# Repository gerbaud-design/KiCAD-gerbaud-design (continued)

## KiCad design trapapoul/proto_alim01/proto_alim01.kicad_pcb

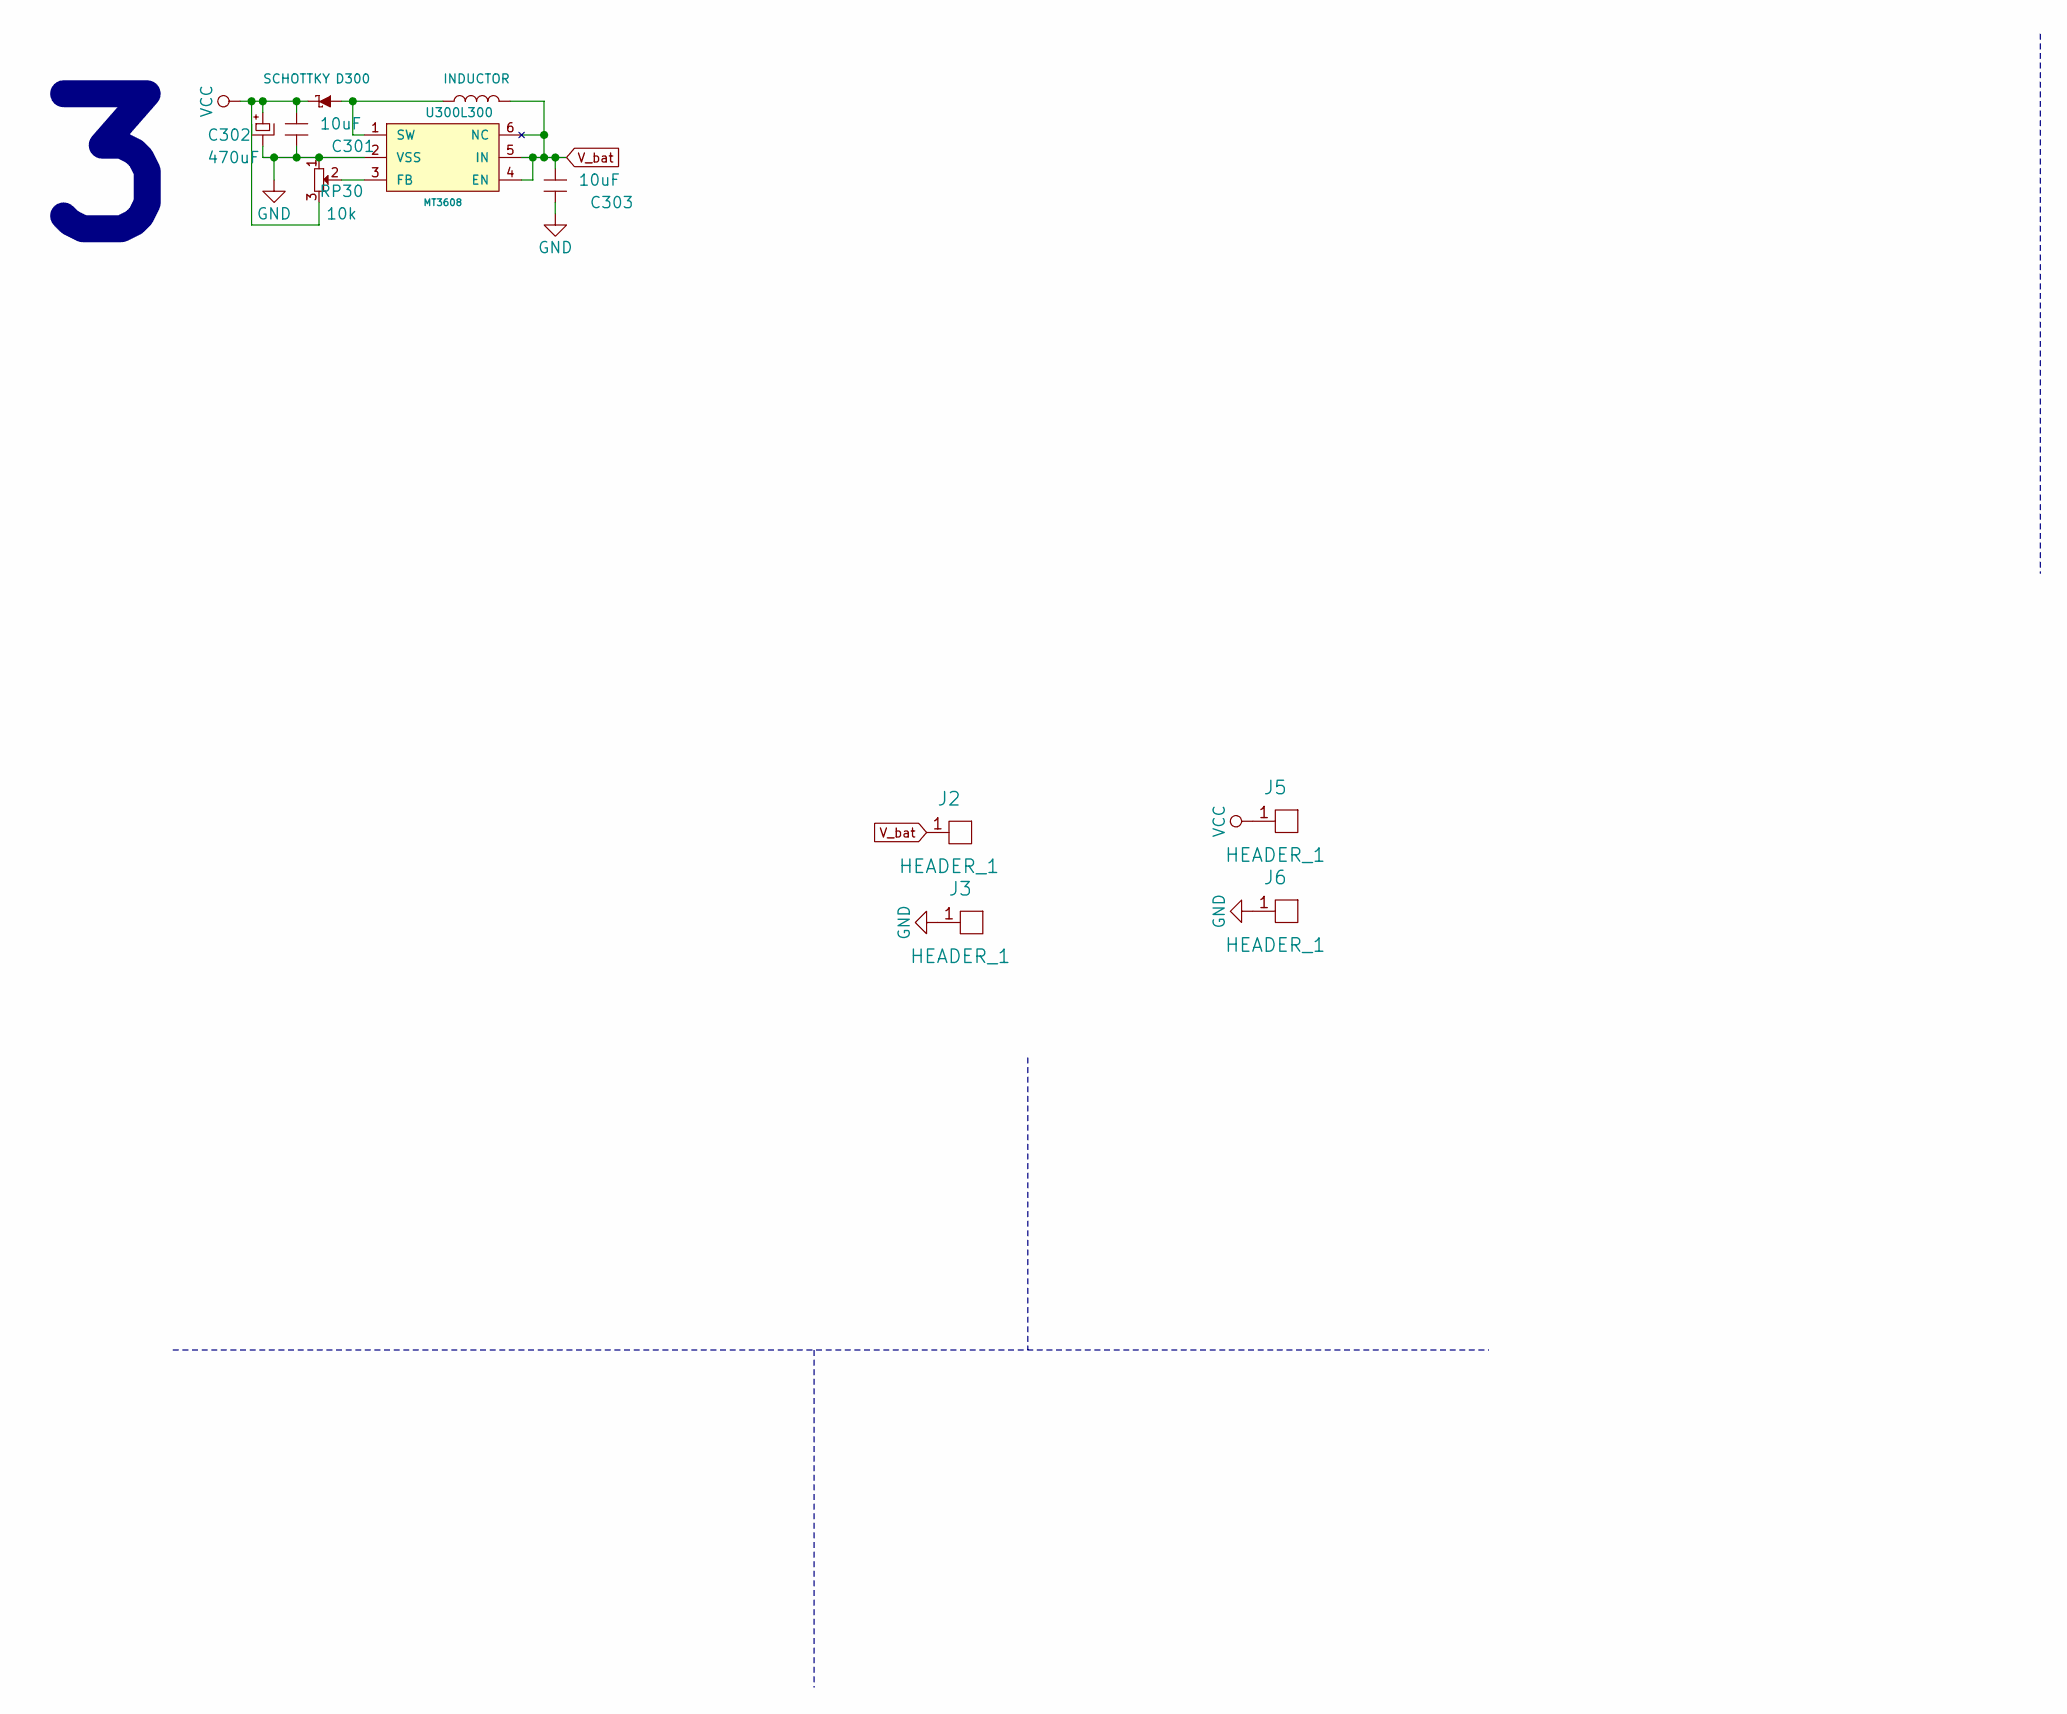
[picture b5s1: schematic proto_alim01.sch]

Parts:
C301, C303: 10uF; C_1206_HandSoldering
C302: 470uF; C_Radial_D8_L11.5_P3.5
D300: SCHOTTKY; MiniMELF_Handsoldering
J2, J3, J5, J6: HEADER_1; Pin_Header_Straight_1x01
L300: INDUCTOR; SELF-WE-PD-XXL
RP30: 10k; Potentiometer_Triwood_RM-065
U300: MT3608; SOT-23-6_Handsoldering

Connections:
GND: C301.2, C302.2, C303.2, J3.1, J6.1, RP30.1, U300.2 (VSS)
unnamed: D300.1 (A), L300.1, U300.1 (SW)
unnamed: RP30.2, U300.3 (FB)
VCC: C301.1, C302.1, D300.2 (K), J5.1, RP30.3
V_bat: C303.1, J2.1, L300.2, U300.4 (EN), U300.5 (IN), U300.6 (NC)

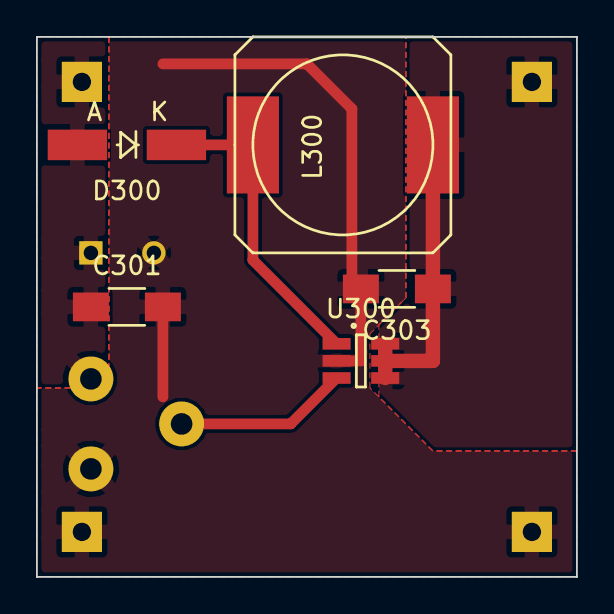
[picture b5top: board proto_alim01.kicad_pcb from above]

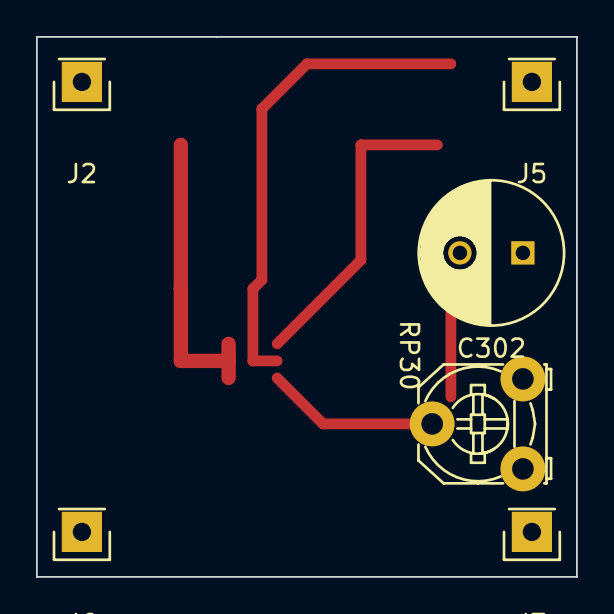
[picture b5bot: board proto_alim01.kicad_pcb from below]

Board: 2 copper layers, 30.0 x 30.0 mm, 11 parts (6 on the bottom side), 5 nets.

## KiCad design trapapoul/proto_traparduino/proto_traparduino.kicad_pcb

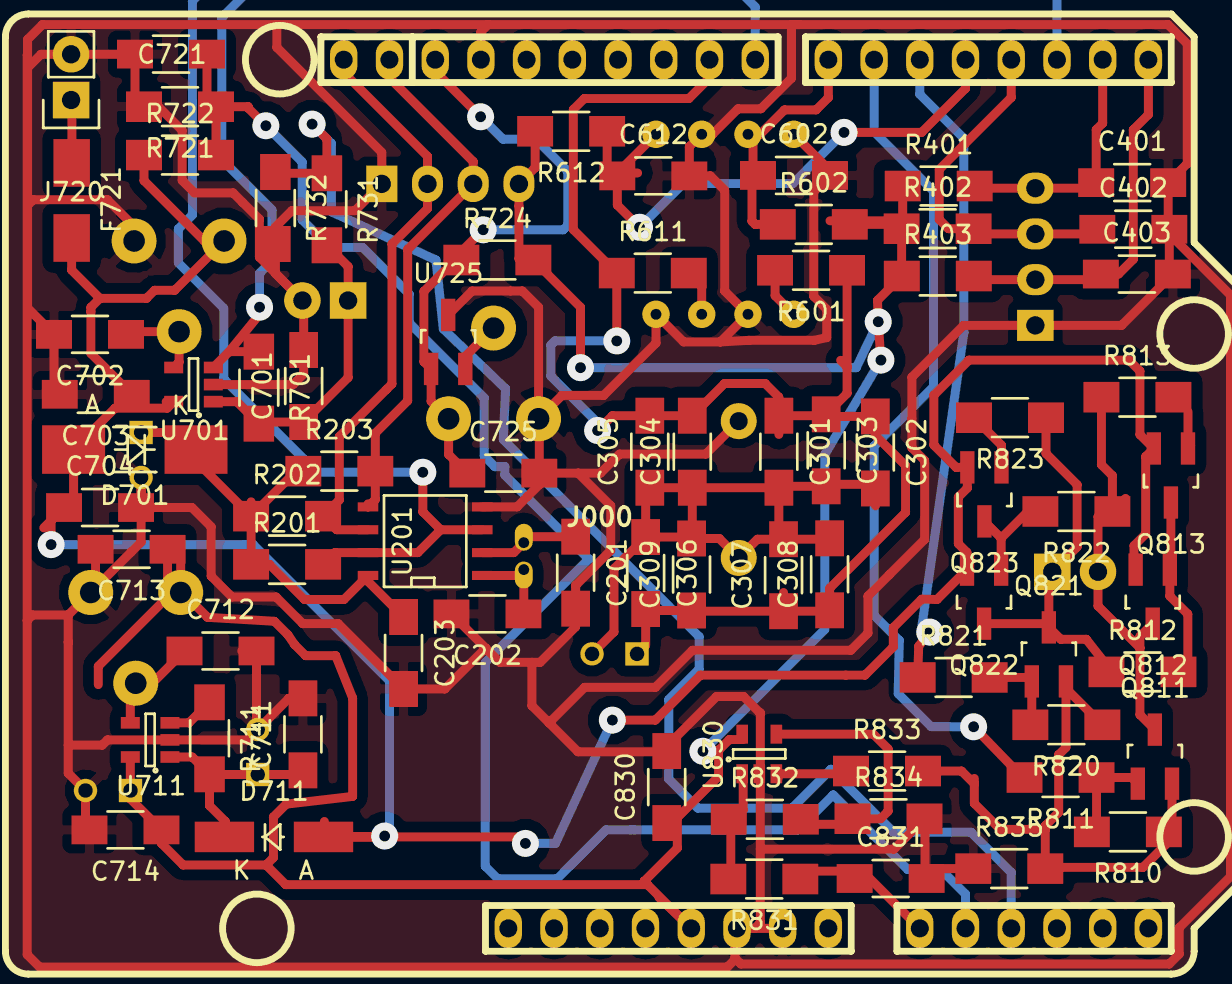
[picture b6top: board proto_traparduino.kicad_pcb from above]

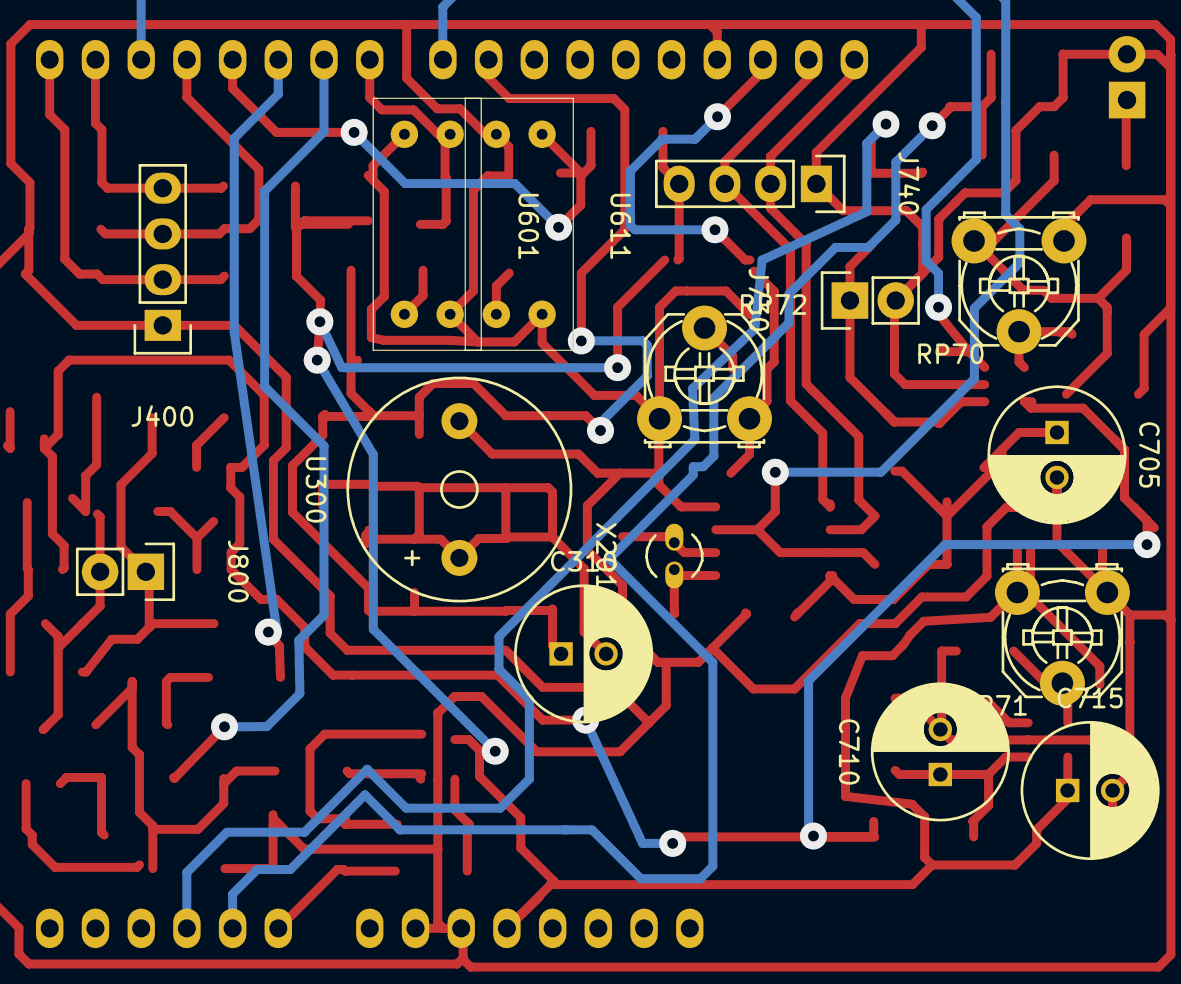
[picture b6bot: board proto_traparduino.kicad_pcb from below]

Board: 2 copper layers, 90 parts (15 on the bottom side), 44 nets.

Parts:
C201, C202: 10p; C_1206_HandSoldering
C203, C401, C402, C403, C721, C725: 10n; C_1206_HandSoldering
C301, C302, C303, C304, C305, C306, C307, C308, C309: 10uF; C_1206_HandSoldering
C310, C705, C710, C715: 220u; C_Radial_D7.5_L11.2_P2.5
C602, C612: 100nF; C_1206_HandSoldering
C701, C704, C711, C714: 10u; C_1206_HandSoldering
C702, C712: 1n; C_1206_HandSoldering
C703, C713, C830, C831: 100n; C_1206_HandSoldering
D701: SCHOTTKY; MELF_Handsoldering
D711: SCHOTTKY; MiniMELF_Handsoldering
F721: 5A; Fuse_SMD1206_HandSoldering
J000: Arduino_Header; arduino_header
J400, J740: HEADER_4; Pin_Header_Straight_1x04
J720, J730, J800: HEADER_2; Pin_Header_Straight_1x02
Q811, Q821: PBSS4320; SOT-23_Handsoldering
Q812, Q813, Q822, Q823: PBSS5350; SOT-23_Handsoldering
R201, R401, R402, R403, R701, R711, R721, R722, R724, R731, R732, R832: 10k; R_1206_HandSoldering
R202, R203: 2.2k; R_1206_HandSoldering
R601, R611: 220; R_1206_HandSoldering
R602, R612: 4k7; R_1206_HandSoldering
R810, R811, R812, R820, R821, R822: 330; R_1206_HandSoldering
R813, R823: 3k3; R_1206_HandSoldering
R831, R833, R834: 1k; R_1206_HandSoldering
R835: 0R2; R_1206_HandSoldering
RP70, RP71: 100k; Potentiometer_Triwood_RM-065
RP72: 10k; Potentiometer_Triwood_RM-065
U201: MCP7940; SOIC-8-N
U300: buzzer; Buzzer_12x9.5RM7.6
U601, U611: ITR9606
U701, U711: MIC5205; SOT-23-5
U725: TLV431-DBZ; SOT-23_Handsoldering
U830: MCP601-SOT; SOT-23-5
X201: 32.768K; Crystal_Round_Vertical_3mm_BigPad

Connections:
BP1: C403.1, J000.15, J400.2, R403.2
BP2: C402.1, J000.18, J400.3, R402.2
BP3: C401.1, J000.16, J400.4, R401.2
C_bkw: J000.20, R821.1
C_frw: J000.21, R811.2
GND: C201.2, C202.2, C203.2, C401.2, C402.2, C403.2, C602.2, C612.2, C701.2, C702.2, C703.2, C704.2, C705.2, C710.2, C711.2, C712.2, C713.2, C714.2, C715.2, C721.2, C725.2, C830.2, C831.2, J000.6, J000.7, J000.29, J400.1, J720.2, J730.2, J740.1, R721.2, R732.2, R834.2, R835.1, RP70.1, RP71.1, RP72.1, U201.4, U300.2, U601.2, U601.4, U611.2, U611.4, U701.2, U711.2, U725.3, U830.2
M_bat: C721.1, J000.10, R721.1, R722.2
M_imot: C831.1, J000.9, R831.1
M_sol: J000.11, R731.1, R732.1
unnamed: C201.1, U201.2, X201.2
unnamed: C202.1, U201.1, X201.1
unnamed: C301.2, C302.2, C303.2, C304.1, C305.1, C306.1, C307.2, C308.2, C309.2, C310.2, U300.1
unnamed: C702.1, RP70.2, U701.4
unnamed: C710.1, C711.1, D711.1, R711.2, U711.1
unnamed: C712.1, RP71.2, U711.4
unnamed: F721.1, J720.1
unnamed: Q811.1, R810.2, R811.1
unnamed: Q811.2, Q821.2, R810.1, R820.1, R833.2, R835.2
unnamed: Q812.1, Q813.3, R812.2
unnamed: Q813.1, R813.2
unnamed: Q821.1, R820.2, R821.2
unnamed: Q822.1, Q823.3, R822.2
unnamed: Q823.1, R823.2
unnamed: R601.2, U601.1
unnamed: R611.2, U611.1
unnamed: R711.1, U711.3
unnamed: R831.2, R832.1, U830.1
unnamed: R832.2, R834.1, U830.4
unnamed: R833.1, U830.3
unnamed: RP72.2, U725.2
SCL: J000.14, J000.32, J740.2, R202.2, U201.6
SDA: J000.13, J000.31, J740.3, R203.2, U201.5
VCC: C713.1, C714.1, C715.1, C830.1, J000.5, J740.4, R401.1, R402.1, R403.1, R602.2, R612.2, R724.2, RP71.3, U711.5, U830.5
V_bat: C703.1, C704.1, D701.2, D711.2, F721.2, Q812.2, Q813.2, Q822.2, Q823.2, R722.1, RP70.3, U701.5
V_ref: C725.1, J000.30, R724.1, RP72.3, U725.1
V_rtc: C203.1, C705.1, D701.1, R201.1, R202.1, R203.1, U201.8
V_sol: C701.1, J730.1, R701.2, R731.2, U701.1
alarm: J000.17, R201.2, U201.3, U201.7
buzz: C301.1, C302.1, C303.1, C304.2, C305.2, C306.2, C307.1, C308.1, C309.1, C310.1, J000.24, R601.1, R611.1
charge_OFF: J000.23, R701.1, U701.3
mot_A: J800.1, Q821.3, Q822.3, R812.1, R823.1
mot_B: J800.2, Q811.3, Q812.3, R813.1, R822.1
quadA: C602.1, J000.22, R602.1, U601.3
quadB: C612.1, J000.19, R612.1, U611.3

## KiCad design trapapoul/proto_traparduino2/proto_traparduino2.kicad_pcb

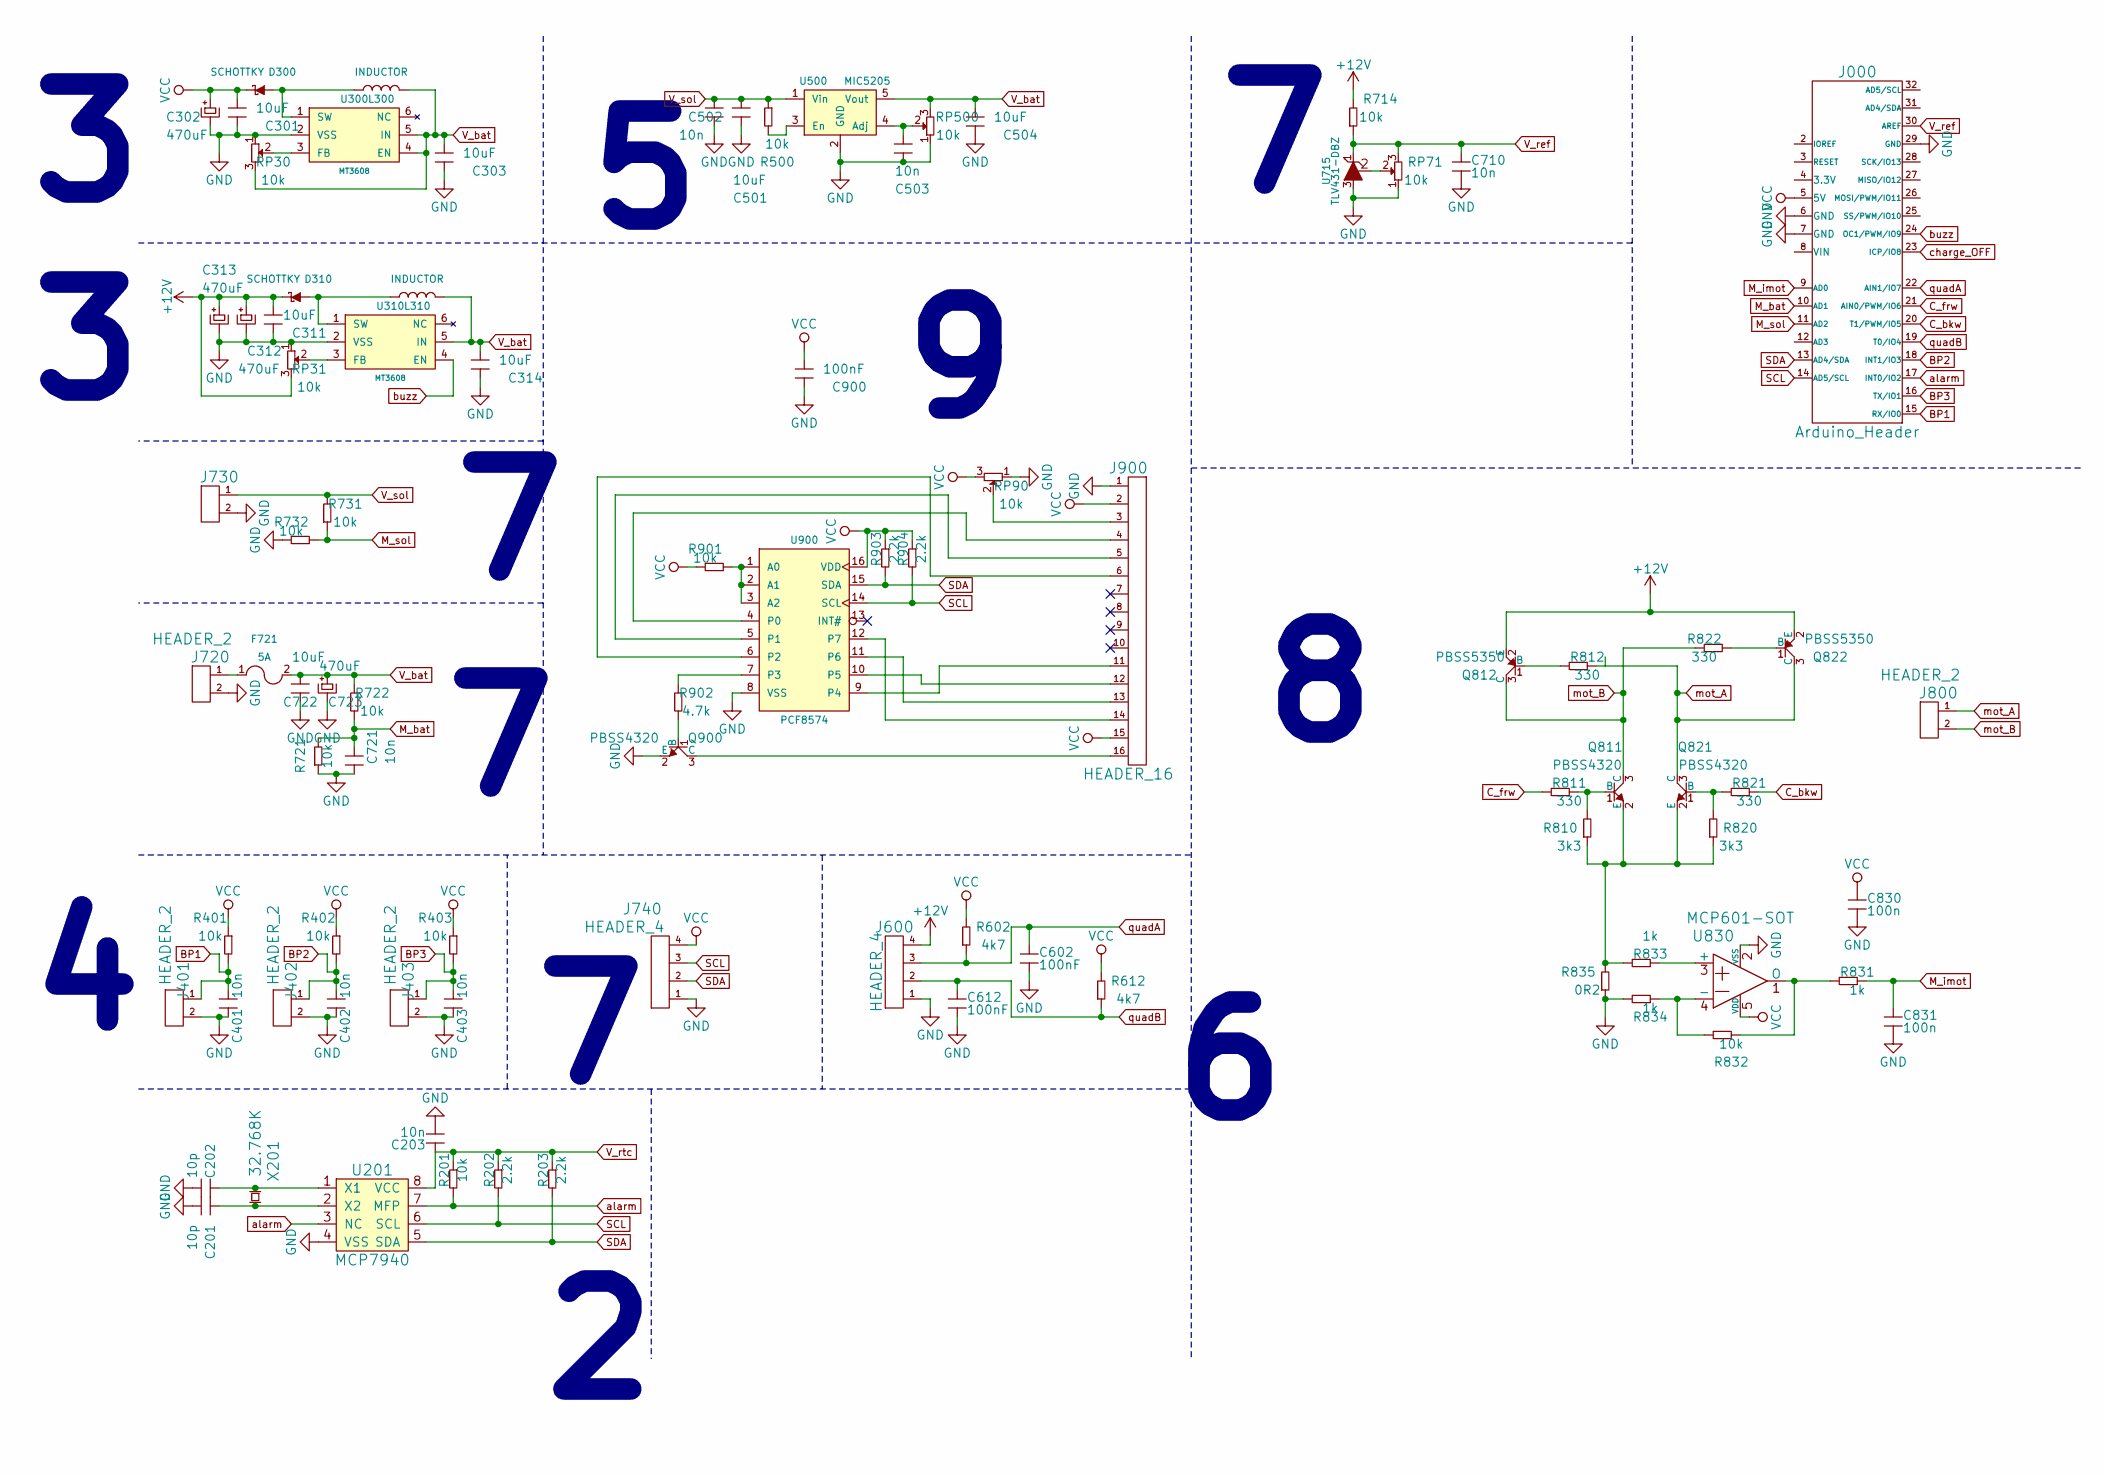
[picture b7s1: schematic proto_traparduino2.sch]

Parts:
C201, C202: 10p; C_1206_HandSoldering
C203, C401, C402, C403, C502, C503, C710, C721: 10n; C_1206_HandSoldering
C301, C303, C311, C314, C501, C504, C722: 10uF; C_1206_HandSoldering
C302, C312, C313, C723: 470uF; C_Radial_D8_L11.5_P3.5
C602, C612, C900: 100nF; C_1206_HandSoldering
C830, C831: 100n; C_1206_HandSoldering
D300, D310: SCHOTTKY; MiniMELF_Handsoldering
F721: 5A; Fuse_SMD1206_HandSoldering
J000: Arduino_Header; arduino_header
J401, J402, J403, J720, J730, J800: HEADER_2; Pin_Header_Straight_1x02
J600, J740: HEADER_4; Pin_Header_Straight_1x04
J900: HEADER_16; Pin_Header_Straight_1x16
L300, L310: INDUCTOR; R_1206_HandSoldering
Q811, Q821, Q900: PBSS4320; SOT-23_Handsoldering
Q812, Q822: PBSS5350; SOT-23_Handsoldering
R201, R401, R402, R403, R500, R714, R721, R722, R731, R732, R832, R901: 10k; R_1206_HandSoldering
R202, R203, R903, R904: 2.2k; R_1206_HandSoldering
R602, R612: 4k7; R_1206_HandSoldering
R810, R820: 3k3; R_1206_HandSoldering
R811, R812, R821, R822: 330; R_1206_HandSoldering
R831, R833, R834: 1k; R_1206_HandSoldering
R835: 0R2; R_1206_HandSoldering
R902: 4.7k; R_1206_HandSoldering
RP30, RP31, RP71, RP90, RP500: 10k; Potentiometer_Triwood_RM-065
U201: MCP7940; SOIC-8-N
U300, U310: MT3608; SOT-23-6_Handsoldering
U500: MIC5205; SOT-23-5_Handsoldering
U715: TLV431-DBZ; SOT-23_Handsoldering
U830: MCP601-SOT; SOT-23-5_Handsoldering
U900: PCF8574; SO-16-W
X201: 32.768K; Crystal_Round_Vertical_3mm_BigPad

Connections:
+12V: C311.1, C312.1, C313.1, D310.2 (K), J600.4, Q812.2 (E), Q822.2 (E), R714.2, RP31.3
BP1: C401.1, J000.15 (RX/IO0), J401.1, R401.2
BP2: C402.1, J000.18 (INT1/IO3), J402.1, R402.2
BP3: C403.1, J000.16 (TX/IO1), J403.1, R403.2
C_bkw: J000.20 (T1/PWM/IO5), R821.1
C_frw: J000.21 (AIN0/PWM/IO6), R811.2
GND: C201.2, C202.2, C203.2, C301.2, C302.2, C303.2, C311.2, C312.2, C313.2, C314.2, C401.2, C402.2, C403.2, C501.2, C502.2, C503.2, C504.2, C602.2, C612.2, C710.2, C721.2, C722.2, C723.2, C830.2, C831.2, C900.2, J000.6 (GND), J000.7 (GND), J000.29 (GND), J401.2, J402.2, J403.2, J600.1, J720.2, J730.2, J740.1, J900.1, Q900.2 (E), R721.1, R732.2, R834.2, R835.1, RP30.1, RP31.1, RP71.1, RP90.1, RP500.1, U201.4 (VSS), U300.2 (VSS), U310.2 (VSS), U500.2 (GND), U715.3 (A), U830.2 (VSS), U900.8 (VSS)
M_bat: C721.1, J000.10 (AD1), R721.2, R722.2
M_imot: C831.1, J000.9 (AD0), R831.1
M_sol: J000.11 (AD2), R731.1, R732.1
unnamed: C201.1, U201.2 (X2), X201.2
unnamed: C202.1, U201.1 (X1), X201.1
unnamed: C503.1, RP500.2, U500.4 (Adj)
unnamed: D300.1 (A), L300.1, U300.1 (SW)
unnamed: D310.1 (A), L310.1, U310.1 (SW)
unnamed: F721.1, J720.1
unnamed: J900.3, RP90.2
unnamed: J900.4, U900.4 (P0)
unnamed: J900.5, U900.5 (P1)
unnamed: J900.6, U900.6 (P2)
unnamed: J900.11, U900.9 (P4)
unnamed: J900.12, U900.10 (P5)
unnamed: J900.13, U900.11 (P6)
unnamed: J900.14, U900.12 (P7)
unnamed: J900.16, Q900.3 (C)
unnamed: Q811.1 (B), R810.2, R811.1
unnamed: Q811.2 (E), Q821.2 (E), R810.1, R820.1, R833.2, R835.2
unnamed: Q812.1 (B), R812.2
unnamed: Q821.1 (B), R820.2, R821.2
unnamed: Q822.1 (B), R822.2
unnamed: Q900.1 (B), R902.2
unnamed: R500.2, U500.3 (En)
unnamed: R831.2, R832.1, U830.1 (O)
unnamed: R832.2, R834.1, U830.4 (-)
unnamed: R833.1, U830.3 (+)
unnamed: R901.1, U900.1 (A0), U900.2 (A1), U900.3 (A2)
unnamed: R902.1, U900.7 (P3)
unnamed: RP30.2, U300.3 (FB)
unnamed: RP31.2, U310.3 (FB)
unnamed: RP71.2, U715.2 (Ref)
SCL: J000.14 (AD5/SCL), J740.3, R202.2, R904.2, U201.6 (SCL), U900.14 (SCL)
SDA: J000.13 (AD4/SDA), J740.2, R203.2, R903.2, U201.5 (SDA), U900.15 (SDA)
VCC: C301.1, C302.1, C830.1, C900.1, D300.2 (K), J000.5 (5V), J740.4, J900.2, J900.15, R401.1, R402.1, R403.1, R602.2, R612.2, R901.2, R903.1, R904.1, RP90.3, U830.5 (VDD), U900.16 (VDD)
V_bat: C303.1, C314.1, C504.1, C722.1, C723.1, F721.2, L300.2, L310.2, R722.1, RP30.3, RP500.3, U300.4 (EN), U300.5 (IN), U310.5 (IN), U500.5 (Vout)
V_ref: C710.1, J000.30 (AREF), R714.1, RP71.3, U715.1 (K)
V_rtc: C203.1, R201.1, R202.1, R203.1, U201.8 (VCC)
V_sol: C501.1, C502.1, J730.1, R500.1, R731.2, U500.1 (Vin)
alarm: J000.17 (INT0/IO2), R201.2, U201.3 (NC), U201.7 (MFP)
buzz: J000.24 (OC1/PWM/IO9), U310.4 (EN)
mot_A: J800.1, Q821.3 (C), Q822.3 (C), R812.1
mot_B: J800.2, Q811.3 (C), Q812.3 (C), R822.1
quadA: C602.1, J000.22 (AIN1/IO7), J600.3, R602.1
quadB: C612.1, J000.19 (T0/IO4), J600.2, R612.1

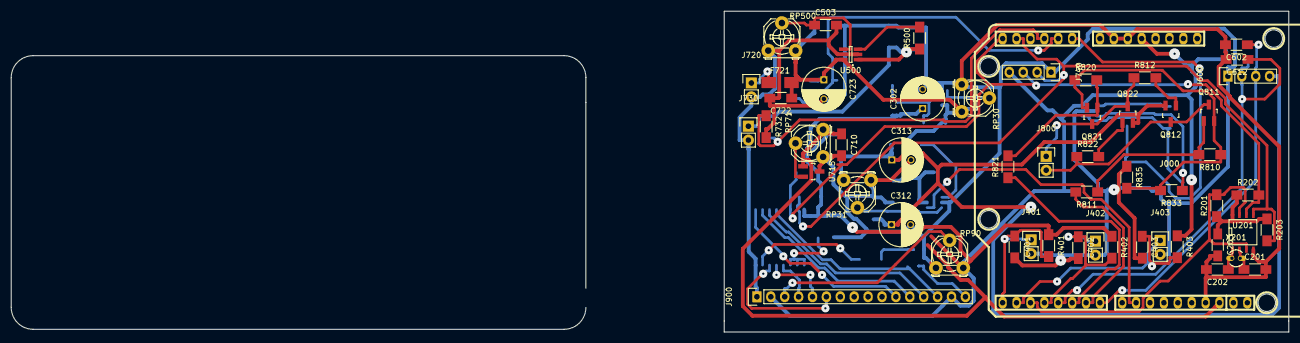
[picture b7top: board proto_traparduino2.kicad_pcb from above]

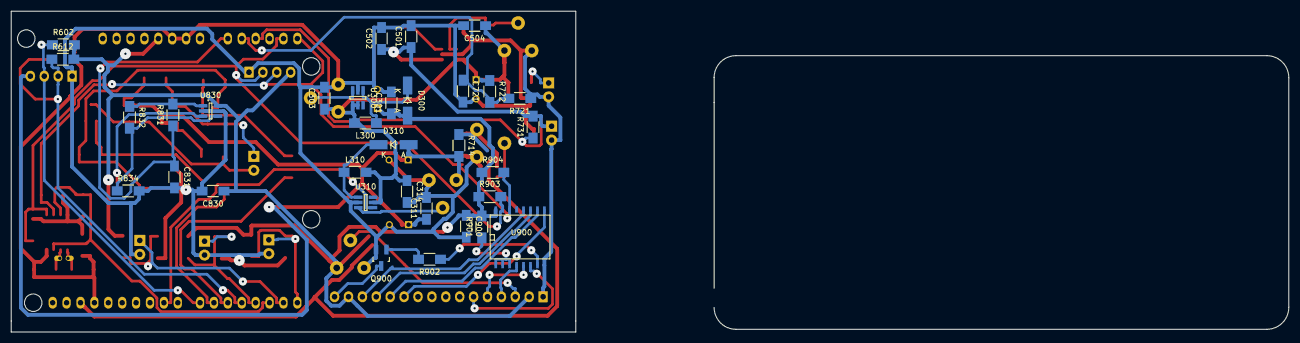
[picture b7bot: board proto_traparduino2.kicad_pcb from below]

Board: 2 copper layers, 103.1 x 58.6 mm, 88 parts (33 on the bottom side), 53 nets.

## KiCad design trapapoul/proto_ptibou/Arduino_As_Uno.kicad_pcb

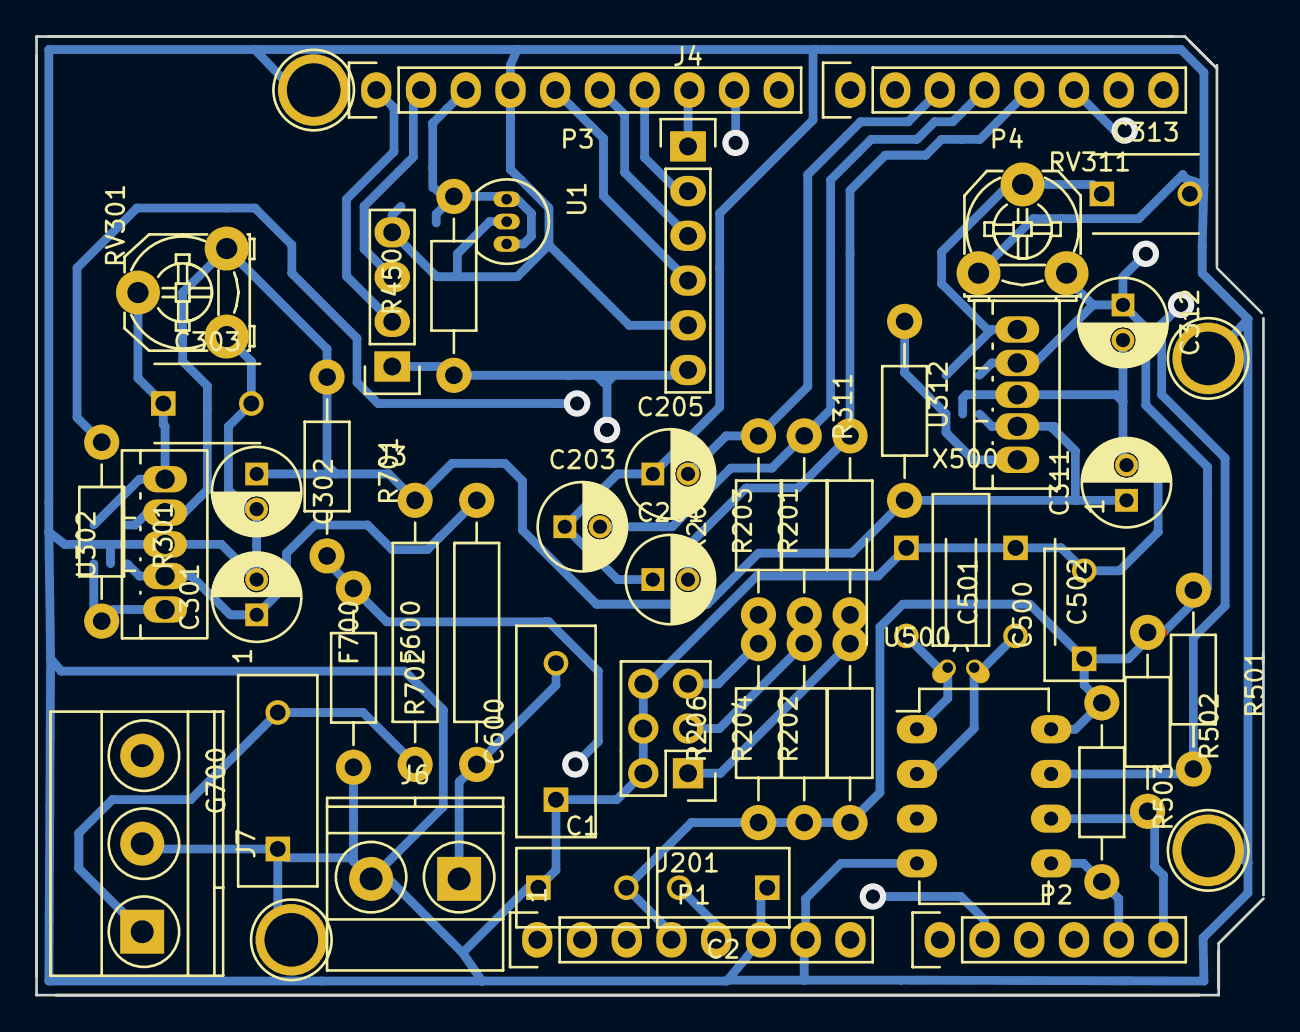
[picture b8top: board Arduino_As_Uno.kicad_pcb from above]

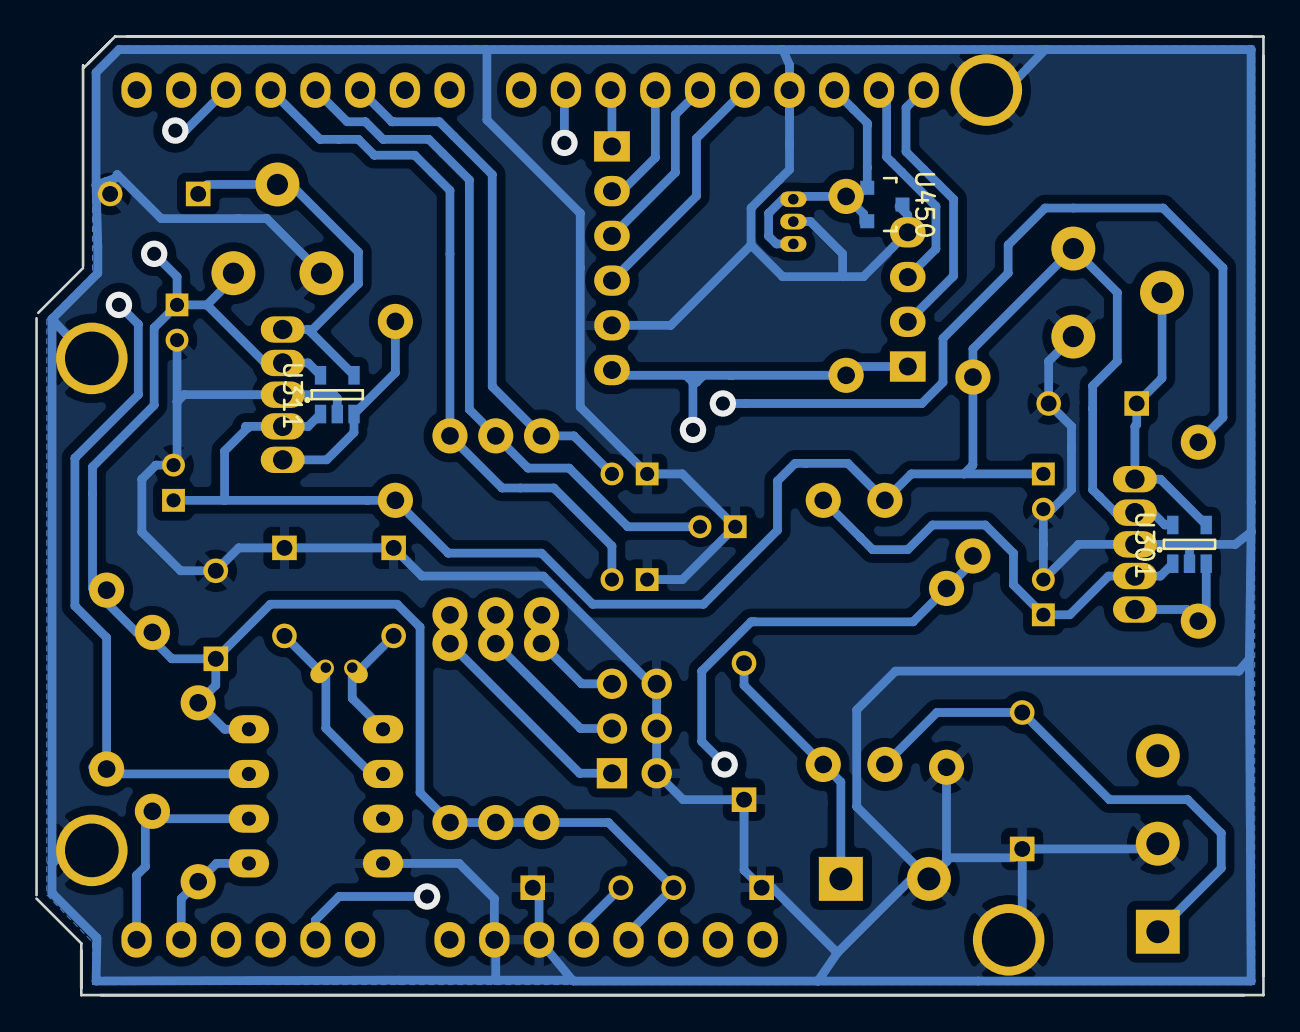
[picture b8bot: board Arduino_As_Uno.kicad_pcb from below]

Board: 4 copper layers, 69.7 x 54.4 mm, 55 parts (3 on the bottom side), 29 nets.

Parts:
C1, C2, C500: 100n; C_Disc_D7.5_P5
C201, C203, C205, C301, C302, C311, C312: 1u; C_Radial_D5_L11_P2
C303: 470pF; C_Disc_D6_P5
C313: 470p; C_Disc_D6_P5
C501, C502: 10p; C_Disc_D6_P5
C600: 100nF; C_Disc_D12_P7.75
C700: 100n; C_Disc_D12_P7.75
F600: 1A; Resistor_Horizontal_RM15mm
F700: 3A; Resistor_Horizontal_RM15mm
J3: CONN_4; Pin_Header_Straight_1x04
J4: CONN_01X06; Pin_Header_Straight_1x06
J6: CONN_2; TerminalBlock_Pheonix_MKDS1.5-2pol
J7: CONN_3; TerminalBlock_Pheonix_MKDS1.5-3pol
J201: CONN_3X2; Pin_Header_Straight_2x03
P1: Power; Socket_Strip_Arduino_1x08
P2: Analog; Socket_Strip_Arduino_1x06
P3: Digital; Socket_Strip_Arduino_1x10
P4: Digital; Socket_Strip_Arduino_1x08
P5, P6, P7, P8: CONN_01X01; Arduino_1pin
R201, R202, R203, R204, R205, R206, R311, R501, R701: 10k; Resistor_Horizontal_RM10mm
R301: 1k; Resistor_Horizontal_RM10mm
R450: 100k; Resistor_Horizontal_RM10mm
R502, R503: 2.2k; Resistor_Horizontal_RM10mm
R702: 4k7; Resistor_Horizontal_RM10mm
RV301, RV311: 200k; Potentiometer_Triwood_RM-065
U1: TL431TH; TO-92_Inline_Narrow_Oval
U301, U311: MIC5205; SOT-23-5
U302, U312: MIC1825; Pentawatt_Neutral_Straight_Vertical_TO220-5-T05A
U450: TL431LP; SOT-23
U500: MCP7940; DIP-8_W7.62mm_LongPads
X500: 32.768KHz; Crystal_Round_Horizontal_3mm_BigPad

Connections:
+3.3V: C1.2, C312.1, C500.1, J3.1, J4.6, P1.4, R202.1, R204.1, R206.1, R450.1, R501.1, R502.1, R503.1, RV311.3, U311.5, U312.4, U500.8
+5V: C2.2, P1.5
A_REF: P3.3, R450.2, U1.1, U1.3, U450.1, U450.2
Alarm_clock: P4.6, R501.2, U500.7
BUTTON_LOW: C205.2, P4.3, R205.2
BUTTON_MID: C203.2, P4.4, R203.2
BUTTON_UP: C201.2, P4.5, R201.2
Charge_ON: P3.9, R301.1
GND: C1.1, C2.1, C201.1, C203.1, C205.1, C301.2, C302.2, C303.2, C311.2, C312.2, C313.2, C500.2, C501.1, C502.1, C600.1, C700.1, J3.4, J4.5, J6.2, J7.2, J201.2, J201.4, J201.6, P1.6, P1.7, P3.4, P5.1, P6.1, P7.1, P8.1, R702.2, RV301.1, RV311.1, U1.2, U301.2, U302.3, U311.2, U312.3, U450.3, U500.4
I2C_SCL: J3.2, P2.6, P3.1, R502.2, U500.6
I2C_SDA: J3.3, P2.5, P3.2, R503.2, U500.5
ICSP2_MISO: J4.3, P3.6
ICSP2_MOSI: J4.2, P3.7
ICSP2_SCK: J4.4, P3.5
Mes_bat: P2.2, R701.2, R702.1
unnamed: C303.1, RV301.2, U301.4, U302.5
unnamed: C313.1, RV311.2, U311.4, U312.5
unnamed: C501.2, U500.1, X500.1
unnamed: C502.2, U500.2, X500.2
unnamed: C600.2, F600.1, J6.1
unnamed: C700.2, F700.1, J7.1
unnamed: J201.1, R201.1, R202.2
unnamed: J201.3, R203.1, R204.2
unnamed: J201.5, R205.1, R206.2
unnamed: R301.2, U301.3, U302.1
unnamed: R311.2, U311.3, U312.1
SDCARD_CS: J4.1, P3.8
V_bat: C302.1, C311.1, F700.2, R311.1, R701.1, RV301.3, U301.5, U302.4, U311.1, U312.2
V_sol: C301.1, F600.2, U301.1, U302.2

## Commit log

2016-03-22 created the license cc by sa 4
    en français and in english
2016-03-22 create folders
    let's see
2016-03-22 schema proto uno
    premier jet du schema
2016-03-23 before rooting
    pcb a été préparé
2016-05-10 unknown changes
2016-05-18 modified library and protopoulie
2016-11-07 trapapoul_proto2 fini
2017-01-31 prototrapapoul4 un peu retouché
2017-04-12 reconnect
